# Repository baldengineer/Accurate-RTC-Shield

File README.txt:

The DS3231 is a Precise Real-Time Clock from Maxim.  It requires almost no external components and is temperature compensated.  This chip solves some of the RTC issues associated with the DS1307.

This Arduino shield will make it simple to add a RTC to any project, especially one where lost time is not acceptable.

On the Eagle design files, there are duplicated holes for all shield pins.  A prototyping area (similar to a breadboard) has been included.  I2C pins are connected to both A4, A5, and the "new" SDA/SCL pins on R3+ boards.

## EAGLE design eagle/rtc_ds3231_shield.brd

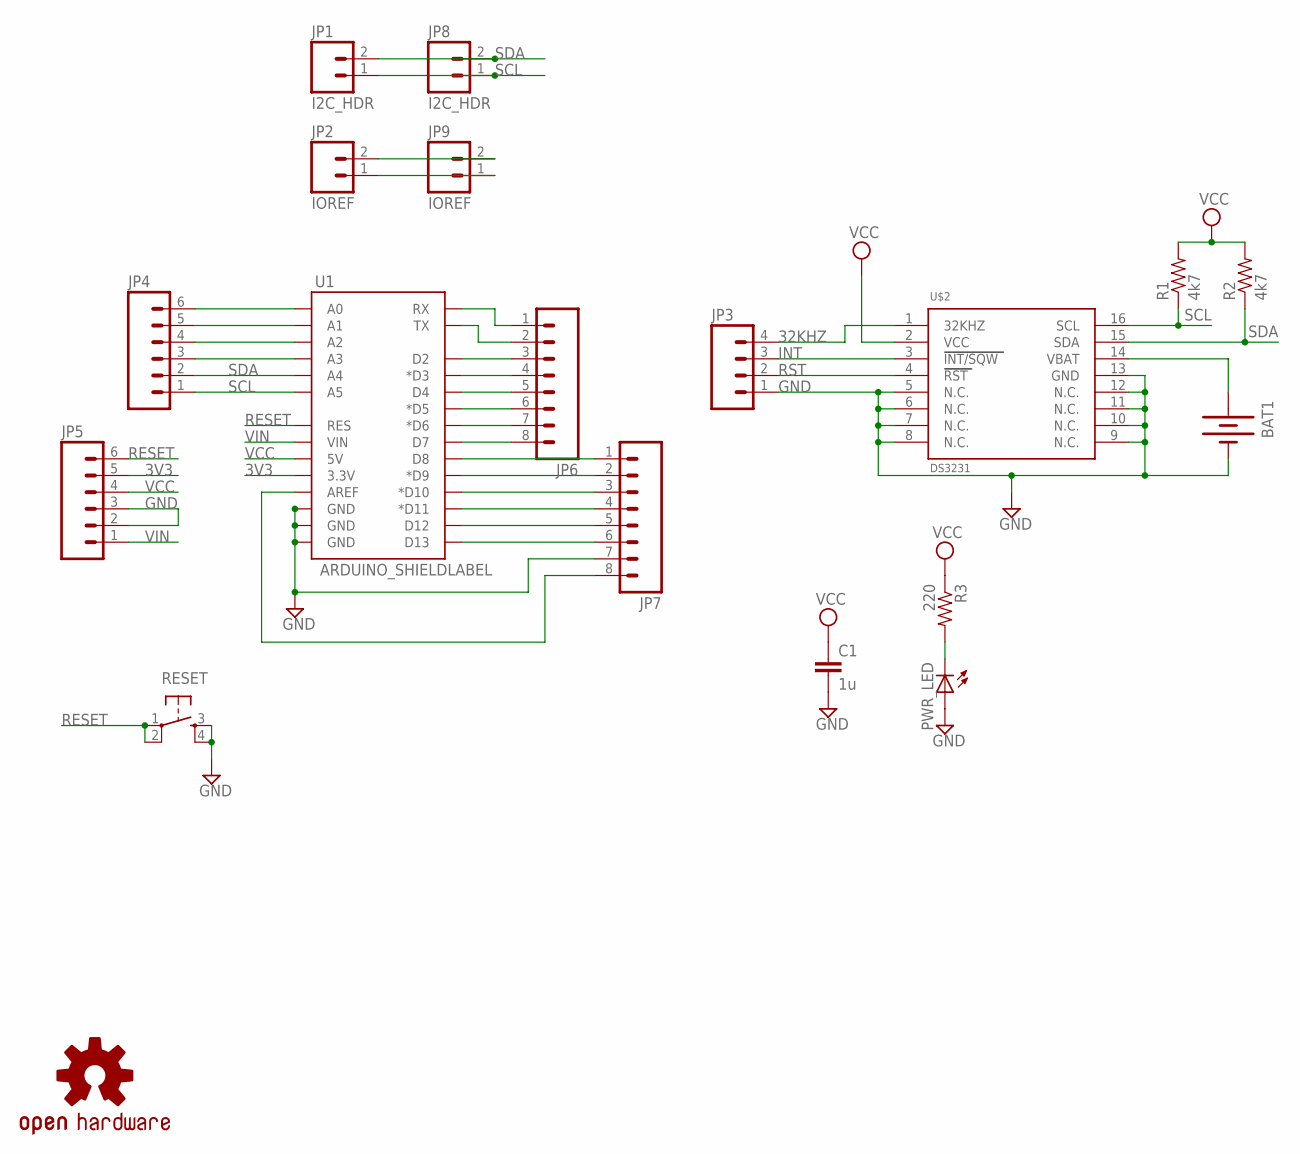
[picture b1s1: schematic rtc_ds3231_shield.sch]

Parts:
BAT1: BATTERY12MM; BATTCON_12MM
C1: 1u; 1206
JP1, JP8: I2C_HDR; 1X02
JP2, JP9: IOREF; 1X02
JP3: M04PTH; 1X04
JP4, JP5: M06SIP; 1X06
JP6, JP7: M081X08; 1X08
PWR_LED: LED1206; LED-1206
R1, R2: 4k7; 1206
R3: 220; 1206
RESET: TAC_SWITCHSMD; TACTILE_SWITCH_SMD
U1: ARDUINO_SHIELDLABEL; UNOR3_SHIELD
U$2: DS3231; SO16L
U$3: OSHW-LOGOM; OSHW-LOGO-M

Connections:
3V3: JP5.5, U1.3.3V
32KHZ: JP3.4, U$2.1 (32KHZ)
GND: BAT1.GND (-), C1.2, JP3.1, JP5.2, JP5.3, JP7.7, PWR_LED.A, RESET.3, RESET.4, U1.GND@0 (GND), U1.GND@1 (GND), U1.GND@2 (GND), U$2.5 (N.C.), U$2.6 (N.C.), U$2.7 (N.C.), U$2.8 (N.C.), U$2.9 (N.C.), U$2.10 (N.C.), U$2.11 (N.C.), U$2.12 (N.C.), U$2.13 (GND)
INT: JP3.3, U$2.3 (INT/SQW)
unnamed: JP4.6, U1.A0
unnamed: JP4.5, U1.A1
unnamed: JP4.4, U1.A2
unnamed: JP4.3, U1.A3
unnamed: PWR_LED.C, R3.2
unnamed: JP6.2, U1.TX
unnamed: JP6.1, U1.RX
unnamed: JP6.3, U1.D2
unnamed: JP6.4, U1.D3 (*D3)
unnamed: JP6.5, U1.D4
unnamed: JP6.6, U1.D5 (*D5)
unnamed: JP6.7, U1.D6 (*D6)
unnamed: JP6.8, U1.D7
unnamed: JP7.1, U1.D8
unnamed: JP7.2, U1.D9 (*D9)
unnamed: JP7.3, U1.D10 (*D10)
unnamed: JP7.4, U1.D11 (*D11)
unnamed: JP7.5, U1.D12
unnamed: JP7.6, U1.D13
unnamed: JP2.2, JP9.2
unnamed: JP7.8, U1.AREF
unnamed: JP2.1, JP9.1
RESET: JP5.6, RESET.1, RESET.2, U1.RES
RST: JP3.2, U$2.4 (RST)
SCL: JP1.1, JP4.1, JP8.1, R1.1, U1.A5, U$2.16 (SCL)
SDA: JP1.2, JP4.2, JP8.2, R2.1, U1.A4, U$2.15 (SDA)
VBAT: BAT1.PWR@2 (+), U$2.14 (VBAT)
VCC: C1.1, JP5.4, R1.2, R2.2, R3.1, U1.5V, U$2.2 (VCC)
VIN: JP5.1, U1.VIN

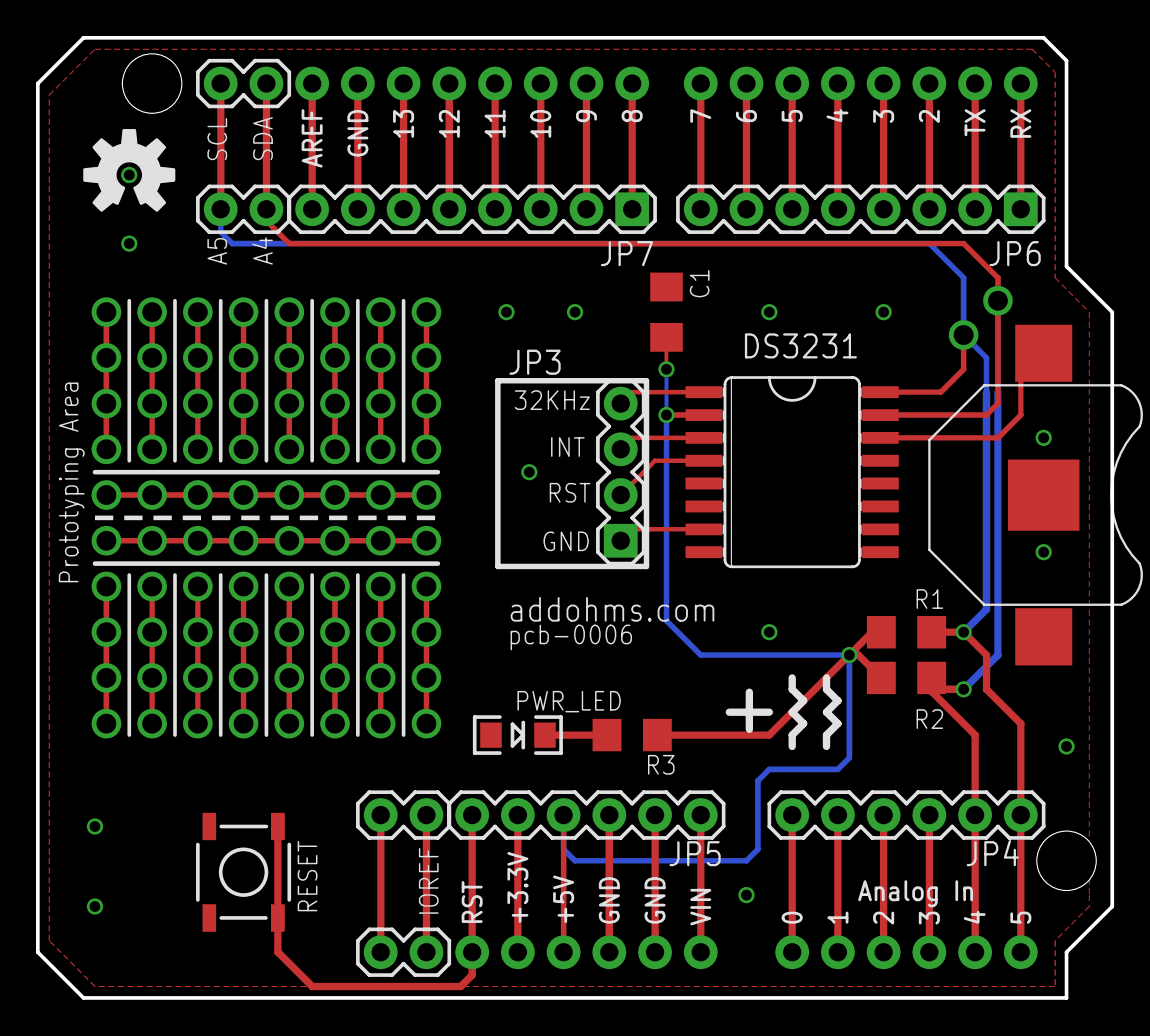
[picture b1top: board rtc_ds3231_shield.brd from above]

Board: 2 copper layers, 59.7 x 53.3 mm, 20 parts (1 on the bottom side), 33 nets.

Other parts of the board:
U$1: OSHW-LOGOM; OSHW-LOGO-M

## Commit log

2012-05-29 Initial Commit
    This is only the Eagle and Shield files. As of 5/28/12 boards have not
    been verified yet.
2012-05-29 2nd Initial Commit
    Typo on the RTC Chip being used.
2012-07-08 Rev1b Updates
    Added LED, RESET Button, some silk screen, cleaned up silkscreen on
    back, made prototyping area clean with 0.1" spacing.
2012-10-15 Minor changes
2012-10-15 Changed silk screen name

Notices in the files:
parts and their libraries:
SparkFun: Licensing: CC v3.0 Share-Alike You are welcome to use this library for commercial purposes.
